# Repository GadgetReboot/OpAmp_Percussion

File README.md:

# OpAmp_Percussion
<br><br><BR><BR>

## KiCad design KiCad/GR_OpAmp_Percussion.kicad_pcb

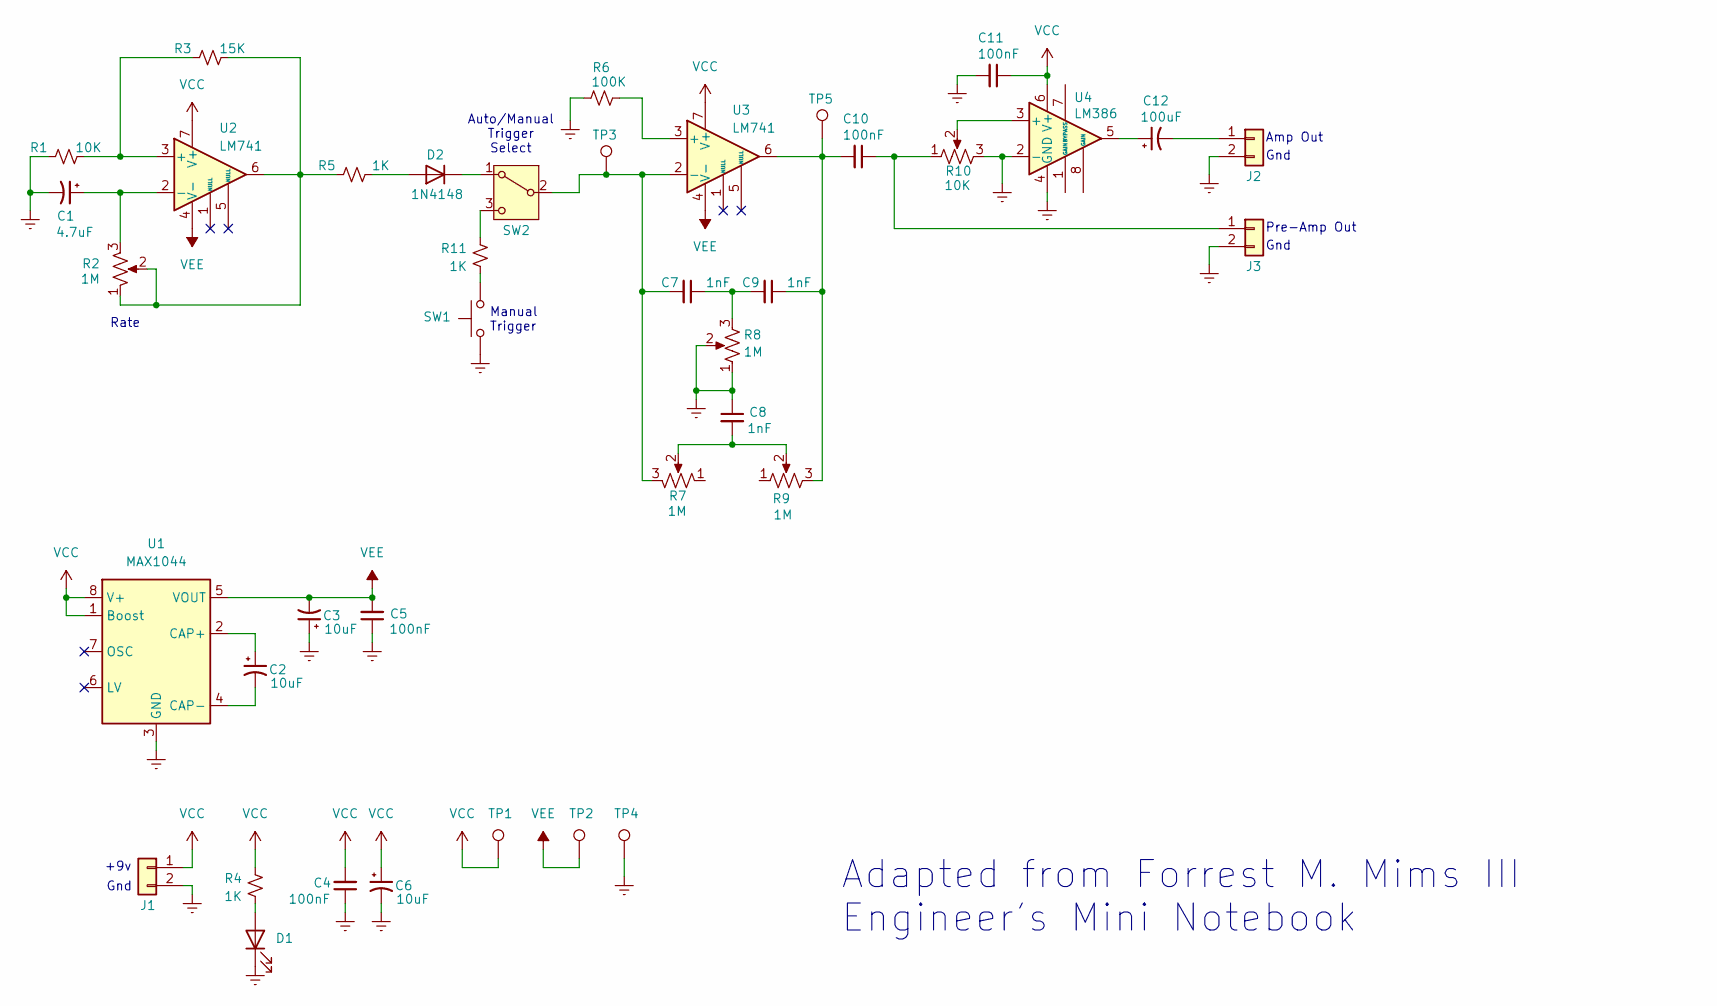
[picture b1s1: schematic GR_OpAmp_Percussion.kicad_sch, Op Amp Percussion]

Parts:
C1: 4.7uF; CP_Radial_D5.0mm_P2.50mm
C2, C3, C6: 10uF; CP_Radial_D5.0mm_P2.50mm
C4, C5, C10, C11: 100nF; C_Disc_D4.7mm_W2.5mm_P5.00mm
C7, C8, C9: 1nF; C_Disc_D4.7mm_W2.5mm_P5.00mm
C12: 100uF; CP_Radial_D5.0mm_P2.50mm
D1: LED; LED_D5.0mm
D2: 1N4148; D_DO-35_SOD27_P7.62mm_Horizontal
J1, J2, J3: Conn_01x02; PinHeader_1x02_P2.54mm_Vertical
R1: 10K; R_Axial_DIN0309_L9.0mm_D3.2mm_P12.70mm_Horizontal
R2, R7, R8, R9: 1M; Pot
R3: 15K; R_Axial_DIN0309_L9.0mm_D3.2mm_P12.70mm_Horizontal
R4, R5, R11: 1K; R_Axial_DIN0309_L9.0mm_D3.2mm_P12.70mm_Horizontal
R6: 100K; R_Axial_DIN0309_L9.0mm_D3.2mm_P12.70mm_Horizontal
R10: 10K; Potentiometer_Bourns_PTV09A-1
SW1: SW_Push; SW_PUSH-12mm_Wuerth-430476085716
SW2: SW_SPDT; PinHeader_1x03_P2.54mm_Vertical
TP1, TP2, TP3, TP4, TP5: TestPoint; TestPoint_Loop_D2.60mm_Drill1.4mm_Beaded
U1: MAX1044; DIP-8_W7.62mm
U2, U3: LM741; DIP-8_W7.62mm
U4: LM386; DIP-8_W7.62mm

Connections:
GNDREF: C1.2, C3.1, C4.1, C5.1, C6.2, C8.1, C11.2, D1.1 (K), J1.2, J2.2, J3.2, R1.2, R6.2, R8.1, R8.2, R10.3, SW1.1, TP4.1, U1.3 (GND), U4.2 (-), U4.4 (GND)
unnamed: C7.1, C9.2, R8.3
unnamed: C8.2, R7.2, R9.2
unnamed: C9.1, C10.2, R9.3, TP5.1, U3.6
unnamed: C12.1, U4.5
unnamed: D1.2 (A), R4.2
unnamed: D2.2 (A), R5.1
unnamed: D2.1 (K), SW2.1 (A)
unnamed: C12.2, J2.1
unnamed: C10.1, J3.1, R10.1
unnamed: R2.1, R2.2, R3.1, R5.2, U2.6
unnamed: R11.2, SW1.2
unnamed: C7.2, R7.3, SW2.2 (B), TP3.1, U3.2 (-)
unnamed: R11.1, SW2.3 (C)
unnamed: C2.1, U1.2 (CAP+)
unnamed: C2.2, U1.4 (CAP-)
unnamed: R1.1, R3.2, U2.3 (+)
unnamed: C1.1, R2.3, U2.2 (-)
unnamed: R6.1, U3.3 (+)
unnamed: R10.2, U4.3 (+)
VCC: C4.2, C6.1, C11.1, J1.1, R4.1, TP1.1, U1.1 (Boost), U1.8 (V+), U2.7 (V+), U3.7 (V+), U4.6 (V+)
VEE: C3.2, C5.2, TP2.1, U1.5 (VOUT), U2.4 (V-), U3.4 (V-)

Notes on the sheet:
+9v
Rate
Manual Trigger
Adapted from Forrest M. Mims III Engineer's Mini Notebook
Amp Out
Pre-Amp Out
Gnd
Auto/Manual Trigger Select

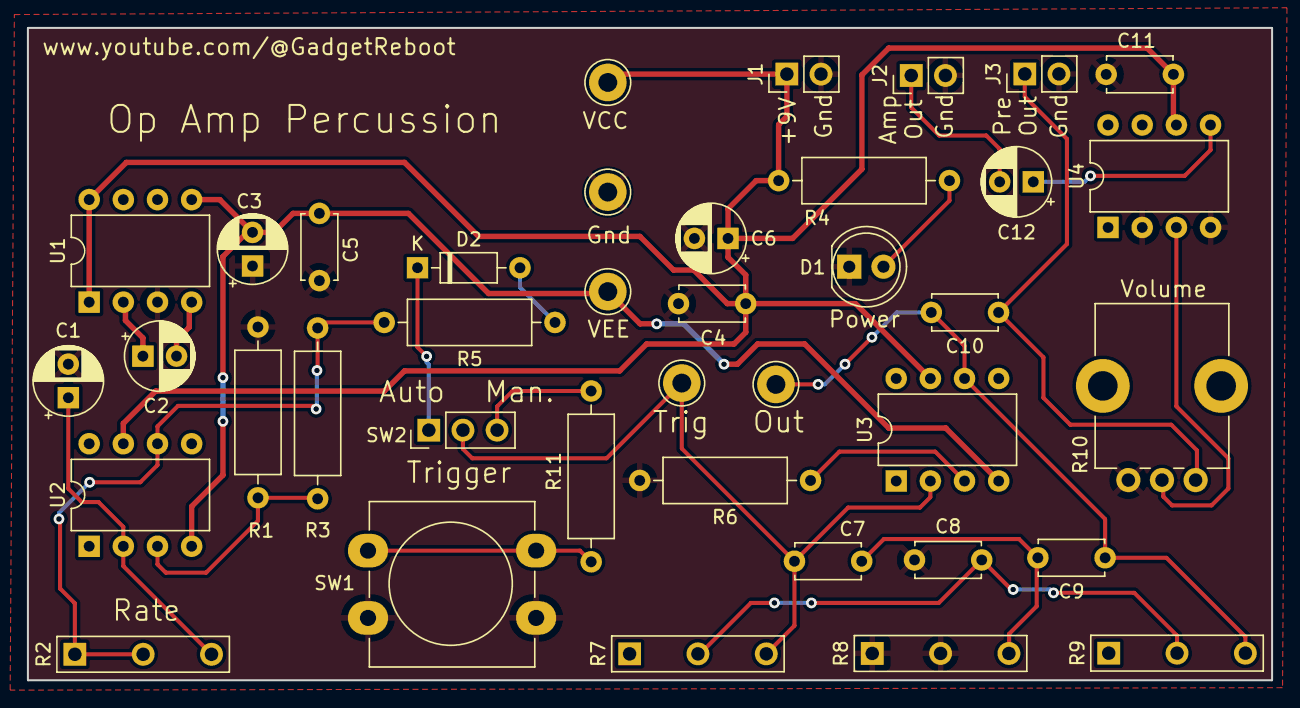
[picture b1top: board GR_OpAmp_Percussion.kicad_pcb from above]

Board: 2 copper layers, 92.5 x 48.5 mm, 39 parts (0 on the bottom side), 22 nets.
